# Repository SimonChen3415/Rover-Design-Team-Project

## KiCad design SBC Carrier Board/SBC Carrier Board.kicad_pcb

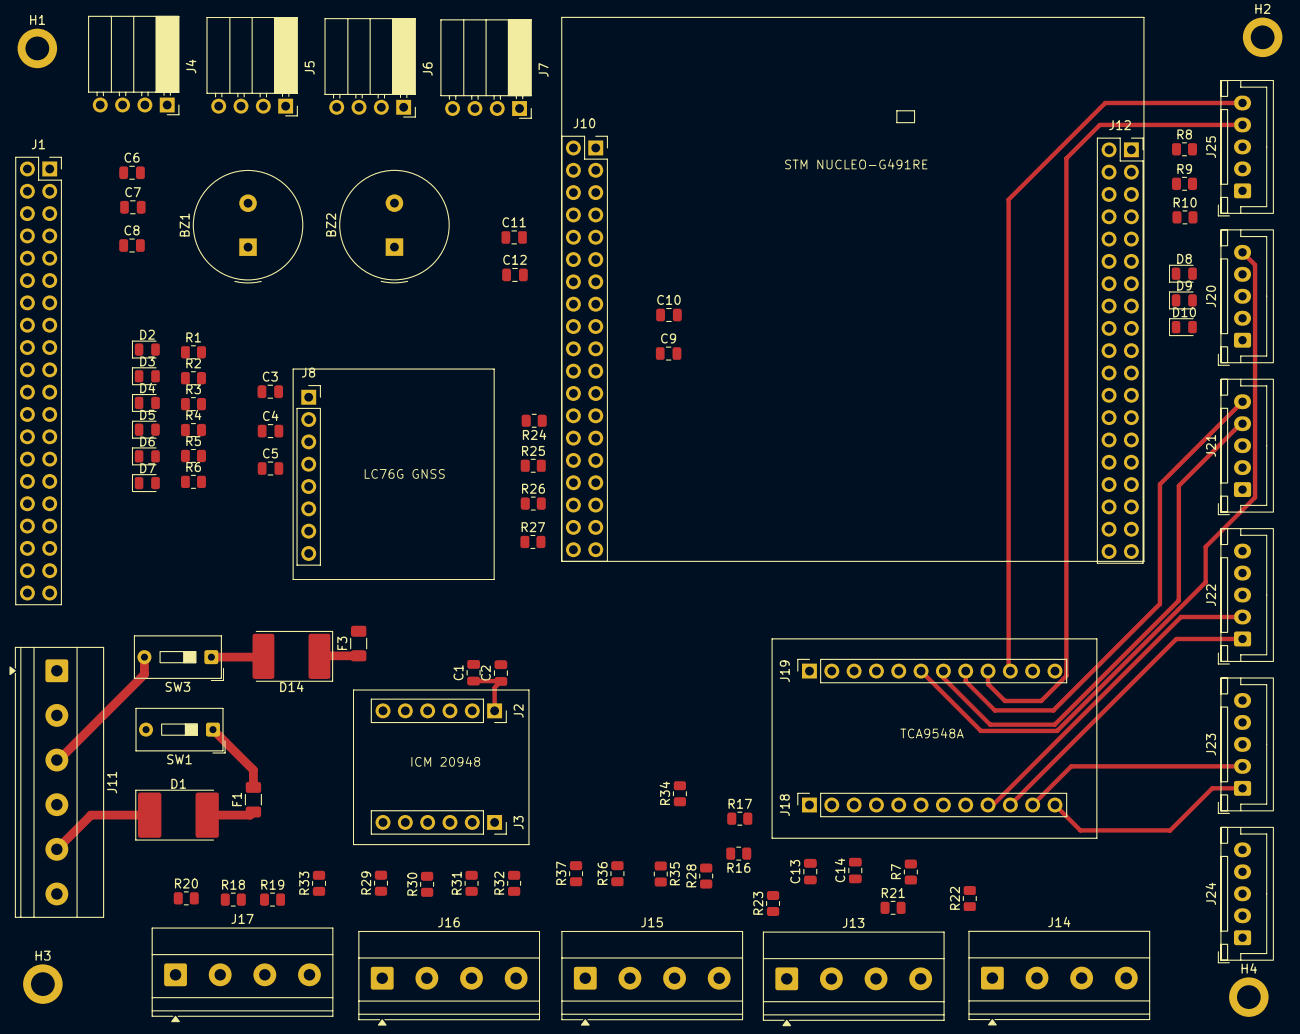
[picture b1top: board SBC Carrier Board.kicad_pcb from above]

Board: 2 copper layers, 91 parts (0 on the bottom side), 72 nets.

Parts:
BZ1, BZ2: Buzzer; Buzzer_TDK_PS1240P02BT_D12.2mm_H6.5mm
C1, C4, C11: 10u; C_0805_2012Metric
C2, C3, C6, C10, C12, C14: 100n; C_0805_2012Metric
C5: 4u7; C_0805_2012Metric
C7: 100u; C_0805_2012Metric
C8, C9: 47u; C_0805_2012Metric
C13: 1u; C_0805_2012Metric
D1: D_Schottky; D_3220_8050Metric_Pad2.65x5.15mm_HandSolder
D2, D3, D4, D5, D6, D7: LED; LED_0805_2012Metric
D8: Status_LED; LED_0805_2012Metric
D9: CAN_LED; LED_0805_2012Metric
D10: Stall_LED; LED_0805_2012Metric
D14: D_Schottky; D_3220_8050Metric
F1, F3: Fuse; Fuse_1206_3216Metric
H1, H2, H3, H4: MountingHole; MountingHole_2.7mm_M2.5_ISO7380_Pad
J1: Conn_02x20_Counter_Clockwise; PinSocket_2x20_P2.54mm_Vertical
J2, J3: Conn_01x06; PinSocket_1x06_P2.54mm_Vertical
J4, J5, J6, J7: Conn_01x04; PinSocket_1x04_P2.54mm_Horizontal
J8: Conn_01x08; PinSocket_1x08_P2.54mm_Vertical
J10: left Morpho CN7; PinSocket_2x19_P2.54mm_Vertical
J11: Screw_Terminal_01x06; TerminalBlock_Phoenix_MKDS-1,5-6-5.08_1x06_P5.08mm_Horizont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
J12: right Morpho CN10; PinSocket_2x19_P2.54mm_Vertical
J13: M1, M2; TerminalBlock_Phoenix_MKDS-1,5-4-5.08_1x04_P5.08mm_Horizont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
J14: M5, M6; TerminalBlock_Phoenix_MKDS-1,5-4-5.08_1x04_P5.08mm_Horizont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
J15: M7, M8; TerminalBlock_Phoenix_MKDS-1,5-4-5.08_1x04_P5.08mm_Horizont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
J16: M9, M10; TerminalBlock_Phoenix_MKDS-1,5-4-5.08_1x04_P5.08mm_Horizont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
J17: M3, M4; TerminalBlock_Phoenix_MKDS-1,5-4-5.08_1x04_P5.08mm_Horizont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
J18, J19: Conn_01x12; PinSocket_1x12_P2.54mm_Vertical
J20, J21, J22, J23, J24, J25: Screw_Terminal_01x05; JST_XH_B5B-XH-A_1x05_P2.50mm_Vertical
R1, R2, R4, R5, R6: 1k; R_0805_2012Metric
R3: 2k; R_0805_2012Metric
R7, R18, R19, R20, R21, R22, R23, R24, R25, R26, R27, R28, R29, R30, R31, R32, R33, R34, R35, R36, R37: 10k; R_0805_2012Metric
R8, R9, R10: 330; R_0805_2012Metric
R16, R17: 4.7k; R_0805_2012Metric
SW1, SW3: SW_DIP_x01; SW_DIP_SPSTx01_Slide_9.78x4.72mm_W7.62mm_P2.54mm

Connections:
+3.3V: C1.1, C2.1, C11.1, C12.1, C13.1, C14.1, J1.1, J1.17 (Pin_9), J2.1, J3.1, J11.1, J18.1, J20.1, J21.1, J22.5, J23.5, J24.5, J25.1, R2.1, R7.1, R16.1, R17.1
+3V3: J4.4, J5.4, J6.4, J7.4
+5.1V: D1.1 (K), D1.2 (A), F1.1, J11.5, R3.2
+5V: C3.1, C4.1, C5.1, J8.1, J11.3, SW3.2
/2.4_Link_ind: J1.29 (Pin_15), R6.2
/DriveMCU/DIR1: J12.29, J13.3, R22.1
/DriveMCU/DIR2: J12.33, J13.1, R34.1
/DriveMCU/DIR3: J12.19, J17.3, R19.1
/DriveMCU/DIR4: J12.21, J17.1, R20.1
/DriveMCU/DIR5: J10.30, J14.3, R25.1
/DriveMCU/DIR6: J10.34, J14.1, R27.1
/DriveMCU/DIR7: J12.15, J15.3, R35.1
/DriveMCU/DIR8: J12.1, J15.1, R37.1
/DriveMCU/DIR9: J10.37, J16.3, R31.1
/DriveMCU/DIR10: J10.1, J16.1, R29.1
/DriveMCU/PWM1: J12.27, J13.4, R21.1
/DriveMCU/PWM2: J12.31, J13.2, R23.1
/DriveMCU/PWM3: J12.25, J17.4, R33.1
/DriveMCU/PWM4: J12.17, J17.2, R18.1
/DriveMCU/PWM5: J10.28, J14.4, R24.1
/DriveMCU/PWM6: J10.32, J14.2, R26.1
/DriveMCU/PWM7: J12.13, J15.4, R28.1
/DriveMCU/PWM8: J12.23, J15.2, R36.1
/DriveMCU/PWM9: J10.35, J16.4, R32.1
/DriveMCU/PWM10: J10.3, J16.2, R30.1
/DriveMCU/RST: J18.5, R7.2
/DriveMCU/SCL: J12.3, J18.4, R16.2
/DriveMCU/SDA: J12.5, J18.3, R17.2
/INT_IMU: J1.11 (Pin_6), J2.6
/LED_fault: J1.16 (Pin_33), R4.2
/LED_status: J1.37 (Pin_19), R1.2
/SCL: J1.5 (Pin_3), J2.4, J8.8
/SDA: J1.3 (Pin_2), J2.5, J8.7
/SIK_Link_ind: J1.31 (Pin_16), R5.2
CAN1_TX: J7.1, J12.12
CAN2_RX: J4.2, J12.14
GND: BZ1.2 (-), BZ2.2 (-), C1.2, C2.2, C3.2, C4.2, C5.2, C6.2, C7.2, C8.2, C9.2, C10.2, C11.2, C12.2, C13.2, C14.2, D2.1 (K), D3.1 (K), D4.1 (K), D5.1 (K), D6.1 (K), D7.1 (K), D8.1 (K), D9.1 (K), D10.1 (K), J1.6 (Pin_38), J1.9 (Pin_5), J1.14 (Pin_34), J1.20 (Pin_31), J1.25 (Pin_13), J1.34 (Pin_24), J1.39 (Pin_20), J2.3, J3.3, J4.3, J5.3, J6.3, J7.3, J8.2, J10.8, J10.19, J10.20, J10.22, J11.2, J11.4, J11.6, J12.7, J12.9, J12.20, J18.2, J18.6, J18.7, J18.8, J20.2, J20.3, J21.2, J21.3, J22.3, J22.4, J23.3, J23.4, J24.3, J24.4, J25.2, J25.3, R18.2, R19.2, R20.2, R21.2, R22.2, R23.2, R24.2, R25.2, R26.2, R27.2, R28.2, R29.2, R30.2, R31.2, R32.2, R33.2, R34.2, R35.2, R36.2, R37.2
GPS_RST: J1.15 (Pin_8), J8.6
unnamed: BZ1.1 (+), J1.18 (Pin_32)
unnamed: BZ2.1 (+), J12.30
unnamed: D2.2 (A), R1.1
unnamed: D3.2 (A), R6.1
unnamed: D4.2 (A), R4.1
unnamed: D5.2 (A), R2.2
unnamed: D6.2 (A), R3.1
unnamed: D7.2 (A), R5.1
unnamed: D8.2 (A), R8.2
unnamed: D9.2 (A), R9.2
unnamed: D10.2 (A), R10.2
unnamed: D14.2 (A), SW3.1
unnamed: D14.1 (K), F3.1
unnamed: F1.2, SW1.1
unnamed: C6.1, C7.1, C8.1, J1.2 (Pin_40), J1.4 (Pin_39), SW1.2
unnamed: C9.1, C10.1, F3.2, J10.6
unnamed: J12.2, R8.1
unnamed: J12.4, R9.1
unnamed: J12.6, R10.1
unnamed: J18.9, J22.2
unnamed: J18.10, J22.1
unnamed: J18.11, J23.2
unnamed: J18.12, J23.1
unnamed: J19.5, J20.4
unnamed: J19.6, J20.5
unnamed: J19.7, J21.4
unnamed: J19.8, J21.5
unnamed: J19.9, J25.4
unnamed: J19.10, J25.5
unnamed: J19.11, J24.1
unnamed: J19.12, J24.2
PPS: J1.13 (Pin_7), J8.5
UART_RX: J1.10 (Pin_36), J8.4
UART_TX: J1.8 (Pin_37), J8.3
